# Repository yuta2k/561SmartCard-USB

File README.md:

# 561SmartCard-USB - Smart Card Module to USB Bridge Board

スマートカード (ISO/IEC 7816) 互換モジュールを USB Type-C デバイスとして扱うための基板です。  
USB-スマートカードブリッジ IC 「SEC1110」を採用しており、CCID 準拠のスマートカードリーダとして動作します。

スマートカード互換モジュールは、USB micro-B または DIP (8 ピン) の 2 種類に対応します。  
DIP 形状のものは実物での確認を行っていないため、嵌合・動作しない可能性があります。

## ディレクトリ構成

- kicad - KiCAD 9 プロジェクト
- gerber_jlcpcb - JLCPCB 製造用ガーバ
- bom - 部品表  
  コンデンサ・抵抗等は、定格を満たせば互換品で問題ありません  
  (基本的に 5V を超える耐圧、1/10W 等)
- images-for-doc - 本ドキュメント用の画像

## 対応スマートカード互換モジュールのピンアサイン

### USB micro-B

1. VCC
2. RST_N
3. CLK
4. IO
5. GND

### DIP

△ が 1 番ピンです (見切れていますが、画像 1 枚目右上)。  
ここから反時計周りに 2, 3, ... 8 番ピンとなります。

1. VCC
2. RST_N
3. CLK
4. C4
5. C8
6. IO
7. NC
8. GND

## 備考

- 手実装を前提に SEC1110 (QFP) の Thermal Pad は反対側の面から半田を流し込めるようにしています
- LED はスマートカードアクセス時に点滅します  
  USB ホストに接続しただけでは点灯・点滅しません
- スマートカード互換モジュールのホットプラグには対応していません  
  USB Type-C ケーブルを抜いてからモジュールを抜き差ししてください

## License

MIT License  
See [LICENSE](./LICENSE) for more details.

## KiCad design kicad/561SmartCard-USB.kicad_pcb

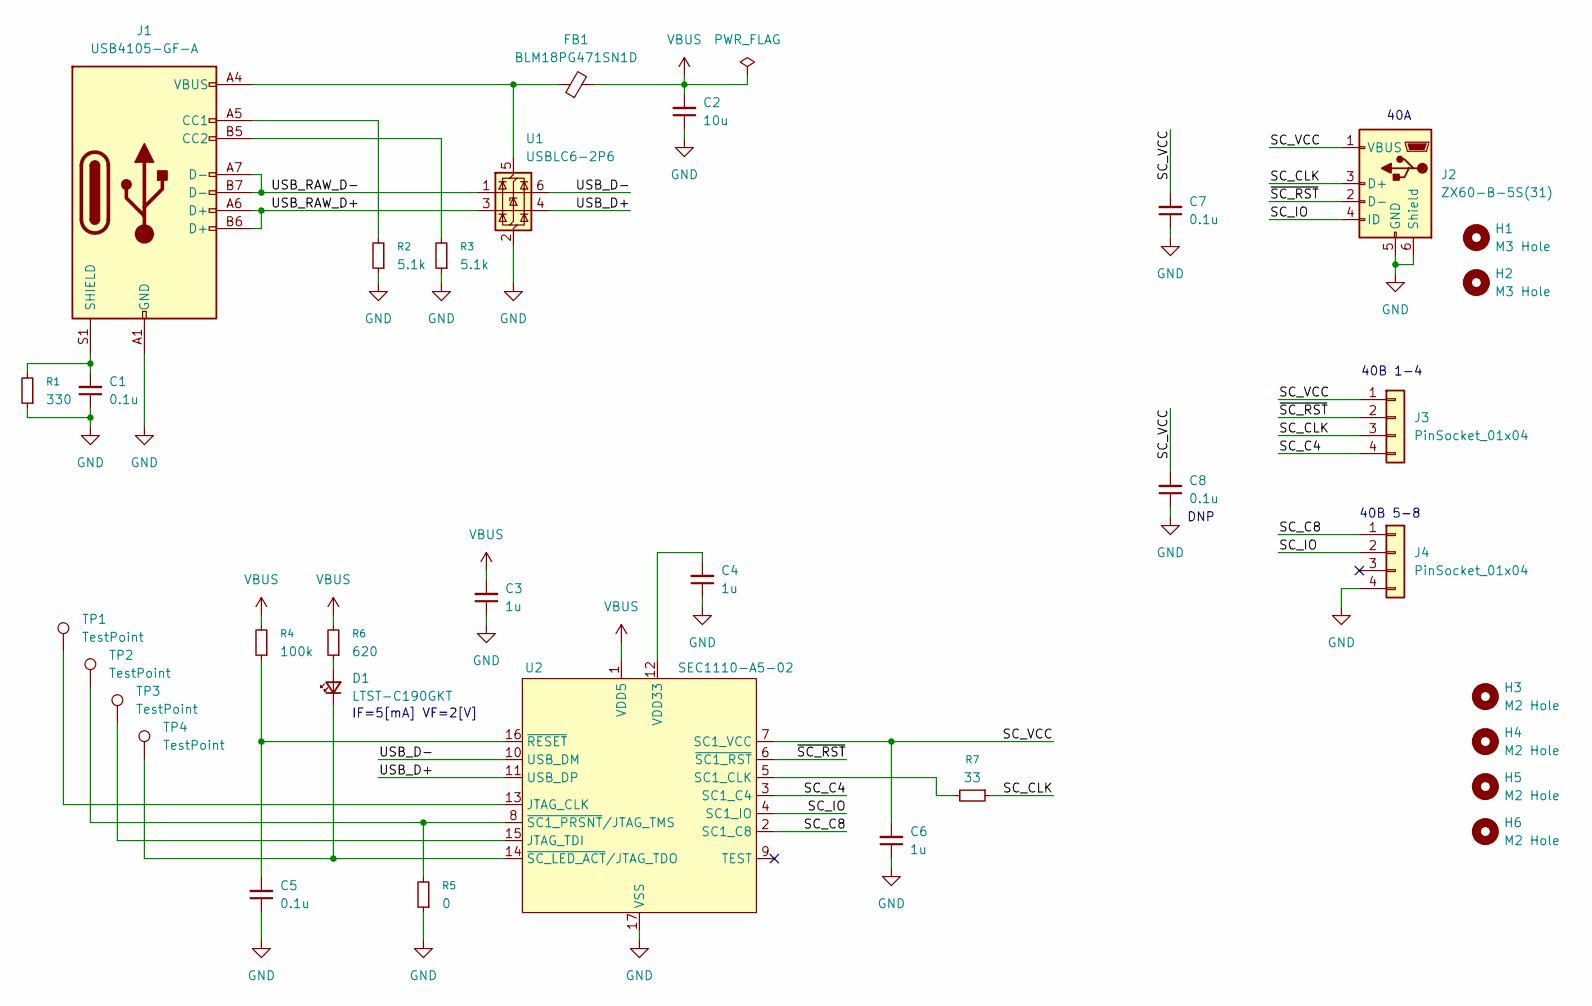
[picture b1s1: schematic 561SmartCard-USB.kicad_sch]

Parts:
C1: 0.1u; C_0805_2012Metric
C2: 10u; C_0805_2012Metric
C3, C4, C6: 1u; C_0402_1005Metric
C5, C7, C8: 0.1u; C_0402_1005Metric
D1: LTST-C190GKT; LED_0603_1608Metric
FB1: BLM18PG471SN1D; L_0603_1608Metric
H1, H2: M3 Hole; MountingHole_3.2mm_M3
H3, H4, H5, H6: M2 Hole; MountingHole_2.2mm_M2
J1: USB4105-GF-A; USB_C_Receptacle_GCT_USB4105-xx-A_16P_TopMnt_Horizontal
J2: ZX60-B-5S(31); USB_Micro-B_Plug_Hirose_ZX60-B-5S(31)
J3, J4: PinSocket_01x04; PinSocket_1x04_P2.54mm_Vertical
R1: 330; R_0805_2012Metric
R2, R3: 5.1k; R_0402_1005Metric
R4: 100k; R_0402_1005Metric
R5: 0; R_0402_1005Metric
R6: 620; R_0402_1005Metric
R7: 33; R_0402_1005Metric
TP1, TP2, TP3, TP4: TestPoint; TestPoint_Pad_D1.0mm
U1: USBLC6-2P6; SOT-666
U2: SEC1110-A5-02; QFN-16-1EP_5x5mm_P0.8mm_EP2.7x2.7mm

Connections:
/SC_C4: J3.4, U2.3 (SC1_C4)
/SC_C8: J4.1, U2.2 (SC1_C8)
/SC_CLK: J2.3 (D+), J3.3, R7.1
/SC_IO: J2.4 (ID), J4.2, U2.4 (SC1_IO)
/SC_VCC: C6.2, C7.2, C8.2, J2.1 (VBUS), J3.1, U2.7 (SC1_VCC)
/USB_D+: U1.4 (I/O2), U2.11 (USB_DP)
/USB_D-: U1.6 (I/O1), U2.10 (USB_DM)
/USB_RAW_D+: J1.A6 (D+), J1.B6 (D+), U1.3 (I/O2)
/USB_RAW_D-: J1.A7 (D-), J1.B7 (D-), U1.1 (I/O1)
/~SC_RST: J2.2 (D-), J3.2, U2.6 (~SC1_RST)
GND: C1.1, C2.1, C3.1, C4.1, C5.1, C6.1, C7.1, C8.1, J1.A1 (GND), J1.A12 (GND), J1.B1 (GND), J1.B12 (GND), J2.5 (GND), J2.6 (Shield), J4.4, R1.1, R2.1, R3.1, R5.1, U1.2 (GND), U2.17 (VSS)
unnamed: D1.2 (A), R6.1
unnamed: D1.1 (K), TP4.1, U2.14 (~SC_LED_ACT/JTAG_TDO)
unnamed: J1.A5 (CC1), R2.2
unnamed: J1.B5 (CC2), R3.2
unnamed: C1.2, J1.S1 (SHIELD), R1.2
unnamed: FB1.1, J1.A4 (VBUS), J1.A9 (VBUS), J1.B4 (VBUS), J1.B9 (VBUS), U1.5 (VBUS)
unnamed: TP1.1, U2.13 (JTAG_CLK)
unnamed: TP3.1, U2.15 (JTAG_TDI)
unnamed: R7.2, U2.5 (SC1_CLK)
unnamed: C4.2, U2.12 (VDD33)
unnamed: C5.2, R4.1, U2.16 (~RESET)
unnamed: R5.2, TP2.1, U2.8 (~SC1_PRSNT/JTAG_TMS)
VBUS: C2.2, C3.2, FB1.2, R4.2, R6.2, U2.1 (VDD5)

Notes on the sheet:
DNP
40A
IF=5[mA] VF=2[V]
40B 5-8
40B 1-4

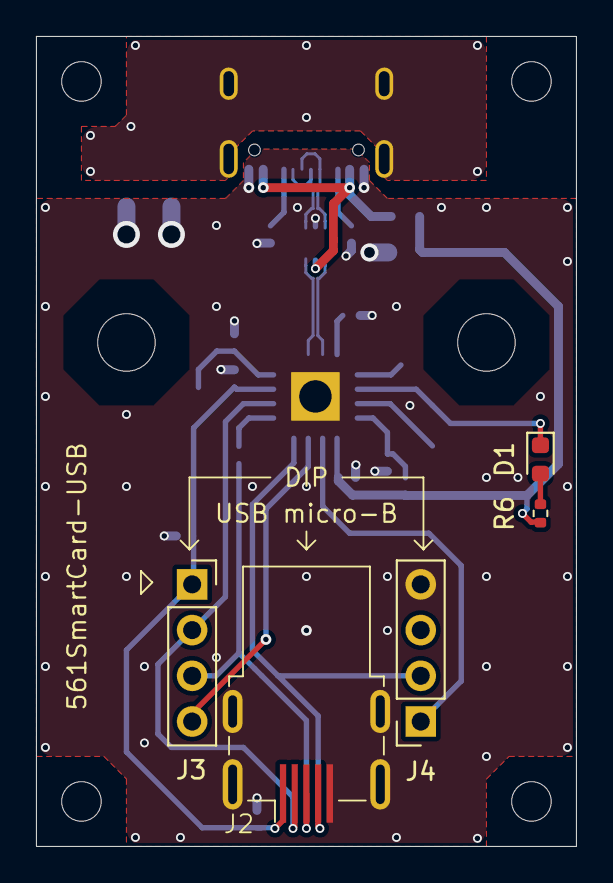
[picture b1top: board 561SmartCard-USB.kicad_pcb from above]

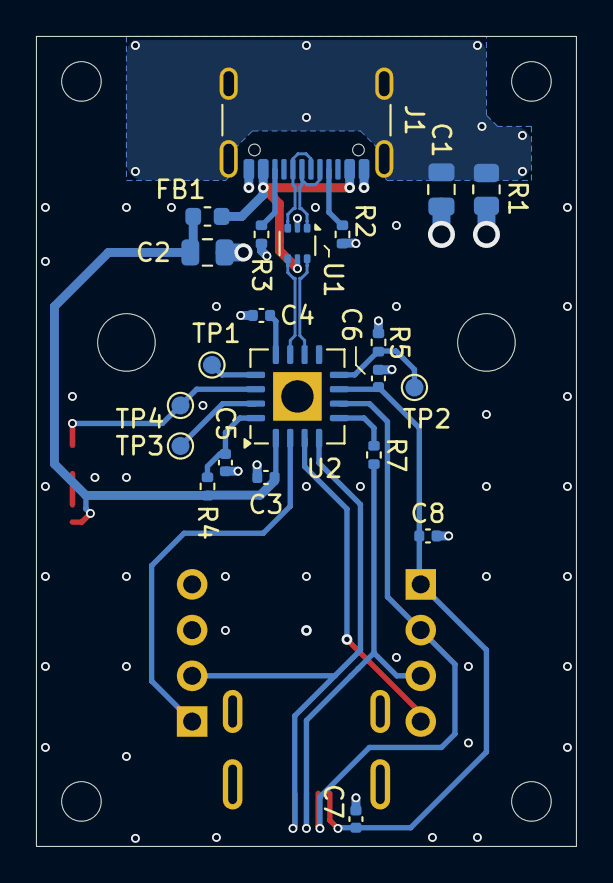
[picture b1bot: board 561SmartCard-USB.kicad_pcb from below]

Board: 4 copper layers, 30.0 x 45.0 mm, 33 parts (22 on the bottom side), 24 nets.

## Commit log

2025-09-14 基板設計・製造用データを追加
2025-09-14 README.md 更新
